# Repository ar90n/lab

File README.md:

# serverless-line-messaging-example

line-messaging example in serverless environment.   
This project acts as echo server in your LINE Talk.

### usage

```
$git clone https://github.com/ar90n/serverless-line-messaging-example.git
$cd serverless-line-messaging-example
$cat > .env
CHANNEL_ID="channel_id"
CHANNEL_SECRET="channel_secret"
CHANNEL_ACCESS_TOKEN="channel_access_token"
$npm install
$serverless deploy
```

### ackonowledge

- [line-messaging](https://github.com/snlangsuan/line-messaging)

### license

MIT. Copyright (c) Masahiro Wada.

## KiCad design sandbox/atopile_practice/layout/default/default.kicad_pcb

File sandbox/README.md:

#my junks
This repository is used for managing my testing codes.
So, these codes may not be work fine.

test [#7](https://github.com/ar90n/lab/issues/7)

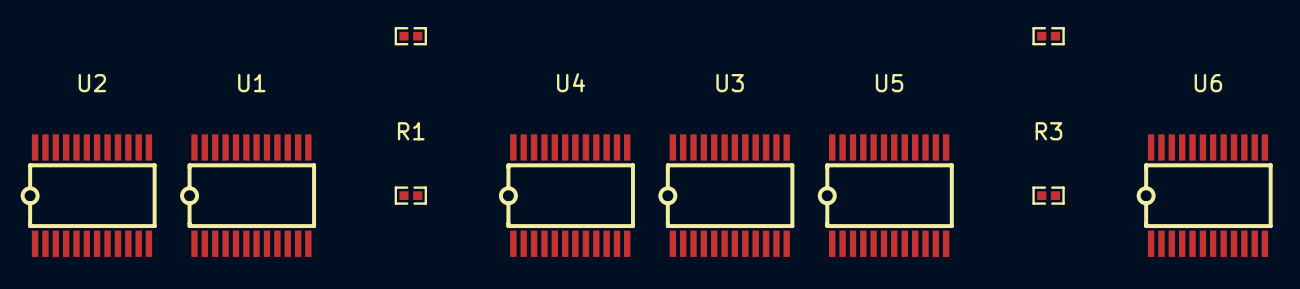
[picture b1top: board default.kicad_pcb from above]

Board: 2 copper layers, 10 parts (0 on the bottom side), 8 nets, no tracks yet.

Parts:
R1, R2, R3, R4: 10kΩ ±1% 62.5mW; R0402
U1, U2, U3, U4, U5, U6: TSSOP-24_L7.8-W4.4-P0.65-LS6.4-BL

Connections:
-i2c_out0_scl: U1.22, U2.5
-i2c_out0_sda: U1.23, U2.4
-i2c_scl-0: R1.1, U2.22, U5.22, U6.5
-i2c_scl-1: R3.1, U1.5, U3.22, U4.22
-i2c_sda-0: R2.1, U2.23, U5.23, U6.4
-i2c_sda-1: R4.1, U1.4, U3.23, U4.23
gnd: U1.12, U1.21, U2.12, U2.21, U3.1, U3.2, U3.12, U4.1, U4.12, U4.21, U5.1, U5.12, U5.21, U6.12
hv: R1.2, R2.2, R3.2, R4.2, U1.1, U1.2, U1.24, U2.1, U2.2, U2.24, U3.21, U3.24, U4.2, U4.24, U5.2, U5.24, U6.24

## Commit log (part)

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2022-09-21 Bump urllib3 from 1.25.9 to 1.26.5 in /sandbox/image_retrieval_practice
    Bumps [urllib3](https://github.com/urllib3/urllib3) from 1.25.9 to 1.26.5.
    - [Release notes](https://github.com/urllib3/urllib3/releases)
    - [Changelog](https://github.com/urllib3/urllib3/blob/main/CHANGES.rst)
    - [Commits](https://github.com/urllib3/urllib3/compare/1.25.9...1.26.5)
    ---
    updated-dependencies:
2022-09-21 Bump urllib3 from 1.25.9 to 1.26.5 in /sandbox/feature-man
    Bumps [urllib3](https://github.com/urllib3/urllib3) from 1.25.9 to 1.26.5.
    - [Release notes](https://github.com/urllib3/urllib3/releases)
    - [Changelog](https://github.com/urllib3/urllib3/blob/main/CHANGES.rst)
    - [Commits](https://github.com/urllib3/urllib3/compare/1.25.9...1.26.5)
    ---
    updated-dependencies:
2022-09-23 Bump protobuf from 3.10.0 to 3.18.3 in /sandbox/kagglebook_practice
    Bumps [protobuf](https://github.com/protocolbuffers/protobuf) from 3.10.0 to 3.18.3.
    - [Release notes](https://github.com/protocolbuffers/protobuf/releases)
    - [Changelog](https://github.com/protocolbuffers/protobuf/blob/main/generate_changelog.py)
    - [Commits](https://github.com/protocolbuffers/protobuf/compare/v3.10.0...v3.18.3)
    ---
    updated-dependencies:
2022-10-12 add assets
2022-10-17 update categories
2022-10-17 add docs
2022-10-22 add toposort
2022-11-04 disable freeze in projects page
2022-11-04 add image
2022-11-07 disable render on hook
2022-11-22 Bump pillow from 9.1.1 to 9.3.0 in /sandbox/step_responses/analysis
    Bumps [pillow](https://github.com/python-pillow/Pillow) from 9.1.1 to 9.3.0.
    - [Release notes](https://github.com/python-pillow/Pillow/releases)
    - [Changelog](https://github.com/python-pillow/Pillow/blob/main/CHANGES.rst)
    - [Commits](https://github.com/python-pillow/Pillow/compare/9.1.1...9.3.0)
    ---
    updated-dependencies:
2022-12-03 Bump decode-uri-component in /sandbox/exercism/reasonml/accumulate
    Bumps [decode-uri-component](https://github.com/SamVerschueren/decode-uri-component) from 0.2.0 to 0.2.2.
    - [Release notes](https://github.com/SamVerschueren/decode-uri-component/releases)
    - [Commits](https://github.com/SamVerschueren/decode-uri-component/compare/v0.2.0...v0.2.2)
    ---
    updated-dependencies:
    - dependency-name: decode-uri-component
2022-12-07 update python_cuda
2022-12-07 Bump decode-uri-component in /sandbox/exercism/reasonml/space-age
    Bumps [decode-uri-component](https://github.com/SamVerschueren/decode-uri-component) from 0.2.0 to 0.2.2.
    - [Release notes](https://github.com/SamVerschueren/decode-uri-component/releases)
    - [Commits](https://github.com/SamVerschueren/decode-uri-component/compare/v0.2.0...v0.2.2)
    ---
    updated-dependencies:
    - dependency-name: decode-uri-component
2022-12-07 Bump qs from 6.5.2 to 6.5.3 in /sandbox/exercism/reasonml/word-count
    Bumps [qs](https://github.com/ljharb/qs) from 6.5.2 to 6.5.3.
    - [Release notes](https://github.com/ljharb/qs/releases)
    - [Changelog](https://github.com/ljharb/qs/blob/main/CHANGELOG.md)
    - [Commits](https://github.com/ljharb/qs/compare/v6.5.2...v6.5.3)
    ---
    updated-dependencies:
2022-12-07 Bump qs from 6.5.2 to 6.5.3 in /sandbox/exercism/reasonml/roman-numerals
    Bumps [qs](https://github.com/ljharb/qs) from 6.5.2 to 6.5.3.
    - [Release notes](https://github.com/ljharb/qs/releases)
    - [Changelog](https://github.com/ljharb/qs/blob/main/CHANGELOG.md)
    - [Commits](https://github.com/ljharb/qs/compare/v6.5.2...v6.5.3)
    ---
    updated-dependencies:
2022-12-07 Bump notebook from 6.0.3 to 6.4.12 in /sandbox/gradient_flow
    Bumps [notebook](http://jupyter.org) from 6.0.3 to 6.4.12.
    ---
    updated-dependencies:
    - dependency-name: notebook
    dependency-type: indirect
    ...
2022-12-08 Bump certifi in /sandbox/image_retrieval_practice
    Bumps [certifi](https://github.com/certifi/python-certifi) from 2020.4.5.1 to 2022.12.7.
    - [Release notes](https://github.com/certifi/python-certifi/releases)
    - [Commits](https://github.com/certifi/python-certifi/compare/2020.04.05.1...2022.12.07)
    ---
    updated-dependencies:
    - dependency-name: certifi
2022-12-08 Bump certifi from 2020.4.5.1 to 2022.12.7 in /sandbox/feature-man
    Bumps [certifi](https://github.com/certifi/python-certifi) from 2020.4.5.1 to 2022.12.7.
    - [Release notes](https://github.com/certifi/python-certifi/releases)
    - [Commits](https://github.com/certifi/python-certifi/compare/2020.04.05.1...2022.12.07)
    ---
    updated-dependencies:
    - dependency-name: certifi
2022-12-09 Bump certifi in /sandbox/solid_python_practice
    Bumps [certifi](https://github.com/certifi/python-certifi) from 2022.9.24 to 2022.12.7.
    - [Release notes](https://github.com/certifi/python-certifi/releases)
    - [Commits](https://github.com/certifi/python-certifi/compare/2022.09.24...2022.12.07)
    ---
    updated-dependencies:
    - dependency-name: certifi
2022-12-18 add cuda practice
2022-12-27 Bump setuptools in /sandbox/step_responses/analysis
    Bumps [setuptools](https://github.com/pypa/setuptools) from 62.3.2 to 65.5.1.
    - [Release notes](https://github.com/pypa/setuptools/releases)
    - [Changelog](https://github.com/pypa/setuptools/blob/main/CHANGES.rst)
    - [Commits](https://github.com/pypa/setuptools/compare/v62.3.2...v65.5.1)
    ---
    updated-dependencies:
2022-12-30 Bump json5 and @glennsl/bs-jest in /sandbox/exercism/reasonml/space-age
    Bumps [json5](https://github.com/json5/json5) to 2.2.2 and updates ancestor dependency [@glennsl/bs-jest](https://github.com/glennsl/bs-jest). These dependencies need to be updated together.
    Updates `json5` from 0.5.1 to 2.2.2
    - [Release notes](https://github.com/json5/json5/releases)
    - [Changelog](https://github.com/json5/json5/blob/main/CHANGELOG.md)
    - [Commits](https://github.com/json5/json5/compare/v0.5.1...v2.2.2)
    Updates `@glennsl/bs-jest` from 0.4.3 to 0.4.10
2022-12-30 Bump json5 and @glennsl/bs-jest in /sandbox/exercism/reasonml/raindrops
    Bumps [json5](https://github.com/json5/json5) to 2.2.2 and updates ancestor dependency [@glennsl/bs-jest](https://github.com/glennsl/bs-jest). These dependencies need to be updated together.
    Updates `json5` from 0.5.1 to 2.2.2
    - [Release notes](https://github.com/json5/json5/releases)
    - [Changelog](https://github.com/json5/json5/blob/main/CHANGELOG.md)
    - [Commits](https://github.com/json5/json5/compare/v0.5.1...v2.2.2)
    Updates `@glennsl/bs-jest` from 0.4.3 to 0.4.10
2023-01-06 Bump json5 and @glennsl/bs-jest in /sandbox/exercism/reasonml/change
    Bumps [json5](https://github.com/json5/json5) to 2.2.3 and updates ancestor dependency [@glennsl/bs-jest](https://github.com/glennsl/bs-jest). These dependencies need to be updated together.
    Updates `json5` from 0.5.1 to 2.2.3
    - [Release notes](https://github.com/json5/json5/releases)
    - [Changelog](https://github.com/json5/json5/blob/main/CHANGELOG.md)
    - [Commits](https://github.com/json5/json5/compare/v0.5.1...v2.2.3)
    Updates `@glennsl/bs-jest` from 0.4.3 to 0.4.10
2023-01-06 Bump json5 and @glennsl/bs-jest in /sandbox/exercism/reasonml/pangram
    Bumps [json5](https://github.com/json5/json5) to 2.2.3 and updates ancestor dependency [@glennsl/bs-jest](https://github.com/glennsl/bs-jest). These dependencies need to be updated together.
    Updates `json5` from 0.5.1 to 2.2.3
    - [Release notes](https://github.com/json5/json5/releases)
    - [Changelog](https://github.com/json5/json5/blob/main/CHANGELOG.md)
    - [Commits](https://github.com/json5/json5/compare/v0.5.1...v2.2.3)
    Updates `@glennsl/bs-jest` from 0.4.3 to 0.4.10
2023-01-06 Bump json5 and @glennsl/bs-jest in /sandbox/exercism/reasonml/raindrops
    Bumps [json5](https://github.com/json5/json5) to 2.2.3 and updates ancestor dependency [@glennsl/bs-jest](https://github.com/glennsl/bs-jest). These dependencies need to be updated together.
    Updates `json5` from 0.5.1 to 2.2.3
    - [Release notes](https://github.com/json5/json5/releases)
    - [Changelog](https://github.com/json5/json5/blob/main/CHANGELOG.md)
    - [Commits](https://github.com/json5/json5/compare/v0.5.1...v2.2.3)
    Updates `@glennsl/bs-jest` from 0.4.3 to 0.4.10
2023-01-06 Bump json5 and @glennsl/bs-jest in /sandbox/exercism/reasonml/leap
    Bumps [json5](https://github.com/json5/json5) to 2.2.3 and updates ancestor dependency [@glennsl/bs-jest](https://github.com/glennsl/bs-jest). These dependencies need to be updated together.
    Updates `json5` from 0.5.1 to 2.2.3
    - [Release notes](https://github.com/json5/json5/releases)
    - [Changelog](https://github.com/json5/json5/blob/main/CHANGELOG.md)
    - [Commits](https://github.com/json5/json5/compare/v0.5.1...v2.2.3)
    Updates `@glennsl/bs-jest` from 0.4.3 to 0.4.10
2023-01-07 add cuda book chapter02
2023-02-07 Bump cryptography from 2.9.2 to 39.0.1 in /sandbox/feature-man
    Bumps [cryptography](https://github.com/pyca/cryptography) from 2.9.2 to 39.0.1.
    - [Release notes](https://github.com/pyca/cryptography/releases)
    - [Changelog](https://github.com/pyca/cryptography/blob/main/CHANGELOG.rst)
    - [Commits](https://github.com/pyca/cryptography/compare/2.9.2...39.0.1)
    ---
    updated-dependencies:
2023-02-11 Bump ipython from 8.3.0 to 8.10.0 in /sandbox/step_responses/analysis
    Bumps [ipython](https://github.com/ipython/ipython) from 8.3.0 to 8.10.0.
    - [Release notes](https://github.com/ipython/ipython/releases)
    - [Commits](https://github.com/ipython/ipython/compare/8.3.0...8.10.0)
    ---
    updated-dependencies:
    - dependency-name: ipython
2023-02-12 add go_todo_app
2023-02-15 add mask.py
2023-02-16 Bump werkzeug from 2.2.2 to 2.2.3 in /sandbox/py_opt_book_practice
    Bumps [werkzeug](https://github.com/pallets/werkzeug) from 2.2.2 to 2.2.3.
    - [Release notes](https://github.com/pallets/werkzeug/releases)
    - [Changelog](https://github.com/pallets/werkzeug/blob/main/CHANGES.rst)
    - [Commits](https://github.com/pallets/werkzeug/compare/2.2.2...2.2.3)
    ---
    updated-dependencies:
2023-02-19 add knn_example
2023-02-19 Bump poetry from 1.0.5 to 1.1.9 in /sandbox/feature-man
    Bumps [poetry](https://github.com/python-poetry/poetry) from 1.0.5 to 1.1.9.
    - [Release notes](https://github.com/python-poetry/poetry/releases)
    - [Changelog](https://github.com/python-poetry/poetry/blob/master/CHANGELOG.md)
    - [Commits](https://github.com/python-poetry/poetry/compare/1.0.5...1.1.9)
    ---
    updated-dependencies:
2023-03-03 Bump minimist, mkdirp and handlebars
    Bumps [minimist](https://github.com/minimistjs/minimist), [mkdirp](https://github.com/isaacs/node-mkdirp) and [handlebars](https://github.com/wycats/handlebars.js). These dependencies needed to be up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
    Updates `minimist` from 1.2.0 to 1.2.8
    - [Release notes](https://github.com/minimistjs/minimist/releases)
    - [Changelog](https://github.com/minimistjs/minimist/blob/main/CHANGELOG.md)
    - [Commits](https://github.com/minimistjs/minimist/compare/v1.2.0...v1.2.8)
    Updates `mkdirp` from 0.5.1 to 0.5.6
2023-03-06 Bump minimist from 1.2.5 to 1.2.8 in /sandbox/wat-mandelbrot
    Bumps [minimist](https://github.com/minimistjs/minimist) from 1.2.5 to 1.2.8.
    - [Release notes](https://github.com/minimistjs/minimist/releases)
    - [Changelog](https://github.com/minimistjs/minimist/blob/main/CHANGELOG.md)
    - [Commits](https://github.com/minimistjs/minimist/compare/v1.2.5...v1.2.8)
    ---
    updated-dependencies:
2023-05-04 add bevy_bullet_practice
2023-05-12 add cadquery samples
2023-05-20 update mnist-zig
2023-06-26 rename zig_practice to zig_mnist
2023-06-28 add build123d practices
2023-07-01 remove zigimg
2023-09-20 add nonlinear_optimization_algorithms
2023-09-23 make more use of sympy expression
2023-09-23 improve profile
2023-09-30 add algebra with symbpy practice
2023-10-18 add jupyter-cadquery
2023-12-29 add models
2024-01-14 add foxglove_bridge docker file
2024-02-10 add ros2 python ai book codes
2024-05-12 update workflow
2024-05-12 updat profile
2024-05-18 add shikkari practice
2024-06-09 add neopixel_ptractice
2024-08-26 add mn_core_practice
2024-09-13 add cp_casts samples
2024-09-24 add mncore challenge codes
2024-12-30 add tinygrad_svm_practice
2025-05-03 add radxa cubie a5e config
2025-05-17 add mcp_paractice
2025-07-12 update and add article
2025-10-10 add esp32_rust_practice
2025-10-14 fix design
2026-01-07 add delaunay_practice
